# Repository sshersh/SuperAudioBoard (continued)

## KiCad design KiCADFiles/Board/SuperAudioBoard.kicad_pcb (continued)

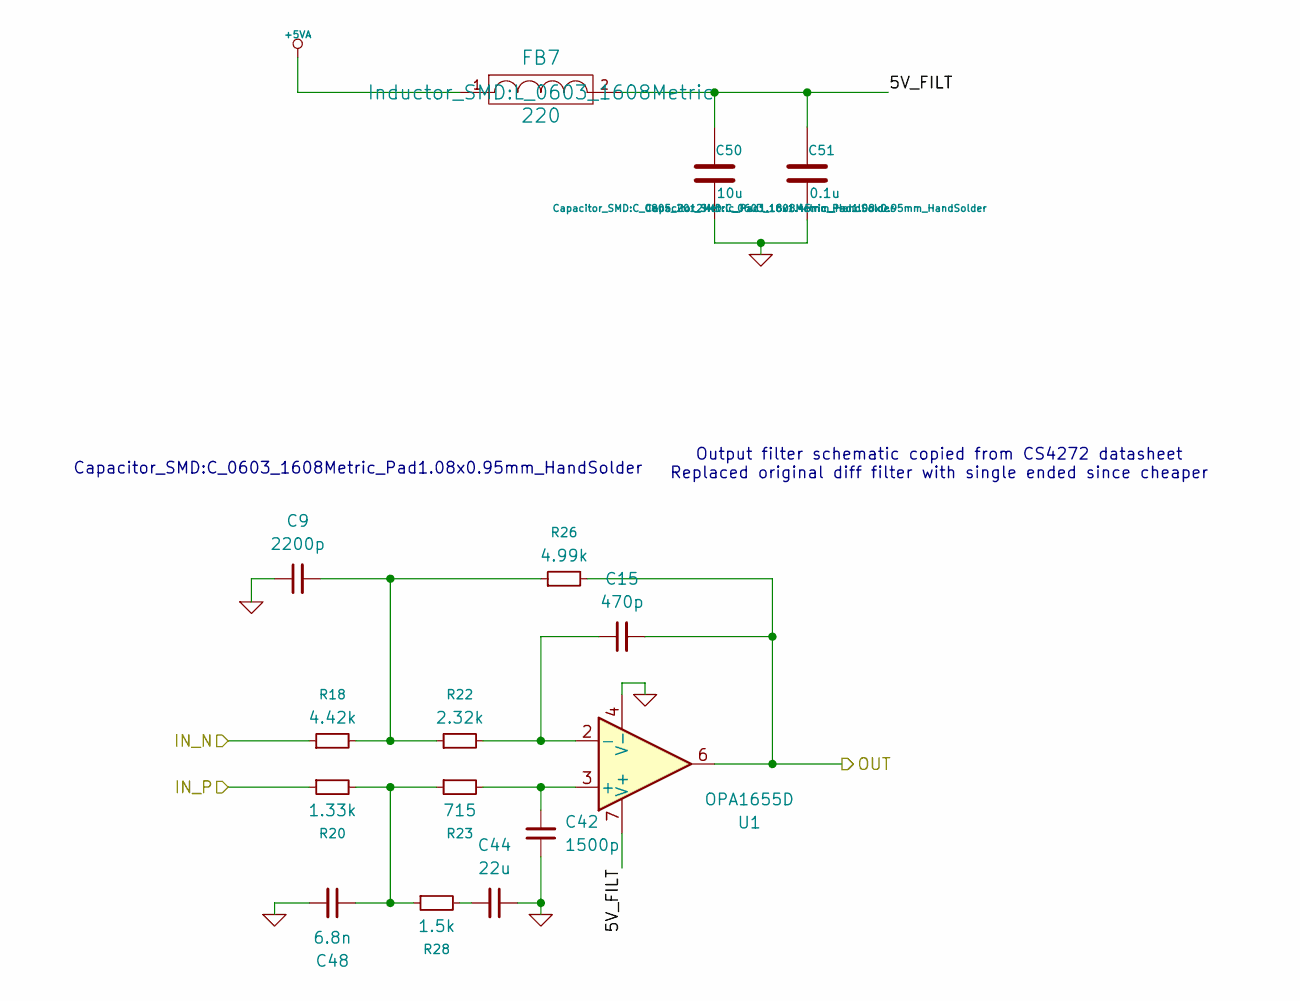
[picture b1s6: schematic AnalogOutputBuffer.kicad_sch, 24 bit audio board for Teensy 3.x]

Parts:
C9: 2200p; C_0603_1608Metric_Pad1.08x0.95mm_HandSolder; MPN GRM1885C1H222JA01D
C15: 470p; C_0603_1608Metric_Pad1.08x0.95mm_HandSolder; MPN 08053C471KAT2A
C42: 1500p; C_0603_1608Metric_Pad1.08x0.95mm_HandSolder; MPN C0603C152F1GACTU
C44: 22u; C_0805_2012Metric_Pad1.18x1.45mm_HandSolder; MPN KAM21AT70J226MU
C48: 6.8n; C_0603_1608Metric_Pad1.08x0.95mm_HandSolder; MPN GRM1885C1H682JA01D
C50: 10u; C_0805_2012Metric_Pad1.18x1.45mm_HandSolder; Voltage 25V; MFG1 PN GRM32DR71E106KA12
C51: 0.1u; C_0603_1608Metric_Pad1.08x0.95mm_HandSolder; MFG1 PN GRM188R71E104KA01
FB7: 220; L_0603_1608Metric; MFG1 PN BLM18AG221SN1
R18: 4.42k; R_0805_2012Metric; MPN ERA-6AEB4421V
R20: 1.33k; R_0805_2012Metric; MPN ERA-6AEB1331V
R22: 2.32k; R_0805_2012Metric; MPN RMCF0805FT2K32
R23: 715; R_0805_2012Metric; MPN RC0805FR-07715RL
R26: 4.99k; R_0805_2012Metric; MPN RG2012P-4991-B-T5
R28: 1.5k; R_0805_2012Metric; MPN RC0805FR-071K5L
U1: OPA1655D; SOIC-8_3.9x4.9mm_P1.27mm; MPN OPA1655D

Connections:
+5VA: FB7.1; also elsewhere on the board
/CodecAndAnalog/OutputBufferB/5V_FILT: C50.1, C51.1, FB7.2, U1.7 (V+)
/CodecAndAnalog/OutputBufferB/IN_N: R18.1; also elsewhere on the board
/CodecAndAnalog/OutputBufferB/IN_P: R20.1; also elsewhere on the board
/CodecAndAnalog/OutputBufferB/OUT: C15.2, R26.2, U1.6; also elsewhere on the board
GND: C9.1, C42.1, C44.1, C48.2, C50.2, C51.2, U1.4 (V-); also elsewhere on the board
unnamed: C9.2, R18.2, R22.1, R26.1
unnamed: C44.2, R28.2
unnamed: C48.1, R20.2, R23.1, R28.1
unnamed: C42.2, R23.2, U1.3 (+)
unnamed: C15.1, R22.2, U1.2 (-)

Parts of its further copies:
C14: 2200p; C_0603_1608Metric_Pad1.08x0.95mm_HandSolder; MPN GRM1885C1H222JA01D
C41: 470p; C_0603_1608Metric_Pad1.08x0.95mm_HandSolder; MPN 08053C471KAT2A
C45: 1500p; C_0603_1608Metric_Pad1.08x0.95mm_HandSolder; MPN C0603C152F1GACTU
C46: 22u; C_0805_2012Metric_Pad1.18x1.45mm_HandSolder; MPN KAM21AT70J226MU
C49: 6.8n; C_0603_1608Metric_Pad1.08x0.95mm_HandSolder; MPN GRM1885C1H682JA01D
C54: 10u; C_0805_2012Metric_Pad1.18x1.45mm_HandSolder; Voltage 25V; MFG1 PN GRM32DR71E106KA12
C55: 0.1u; C_0603_1608Metric_Pad1.08x0.95mm_HandSolder; MFG1 PN GRM188R71E104KA01
FB8: 220; L_0603_1608Metric; MFG1 PN BLM18AG221SN1
R19: 4.42k; R_0805_2012Metric; MPN ERA-6AEB4421V
R21: 1.33k; R_0805_2012Metric; MPN ERA-6AEB1331V
R24: 2.32k; R_0805_2012Metric; MPN RMCF0805FT2K32
R25: 715; R_0805_2012Metric; MPN RC0805FR-07715RL
R27: 4.99k; R_0805_2012Metric; MPN RG2012P-4991-B-T5
R29: 1.5k; R_0805_2012Metric; MPN RC0805FR-071K5L
U4: OPA1655D; SOIC-8_3.9x4.9mm_P1.27mm; MPN OPA1655D

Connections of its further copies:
+5VA: FB8.1; also elsewhere on the board
/CodecAndAnalog/OutputBufferA/5V_FILT: C54.1, C55.1, FB8.2, U4.7 (V+)
/CodecAndAnalog/OutputBufferA/IN_N: R19.1; also elsewhere on the board
/CodecAndAnalog/OutputBufferA/IN_P: R21.1; also elsewhere on the board
/CodecAndAnalog/OutputBufferA/OUT: C41.2, R27.2, U4.6; also elsewhere on the board
GND: C14.1, C45.1, C46.1, C49.2, C54.2, C55.2, U4.4 (V-); also elsewhere on the board
unnamed: C14.2, R19.2, R24.1, R27.1
unnamed: C46.2, R29.2
unnamed: C49.1, R21.2, R25.1, R29.1
unnamed: C45.2, R25.2, U4.3 (+)
unnamed: C41.1, R24.2, U4.2 (-)

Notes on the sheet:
Capacitor_SMD:C_0603_1608Metric_Pad1.08x0.95mm_HandSolder
Output filter schematic copied from CS4272 datasheet Replaced original diff filter with single ended since cheaper

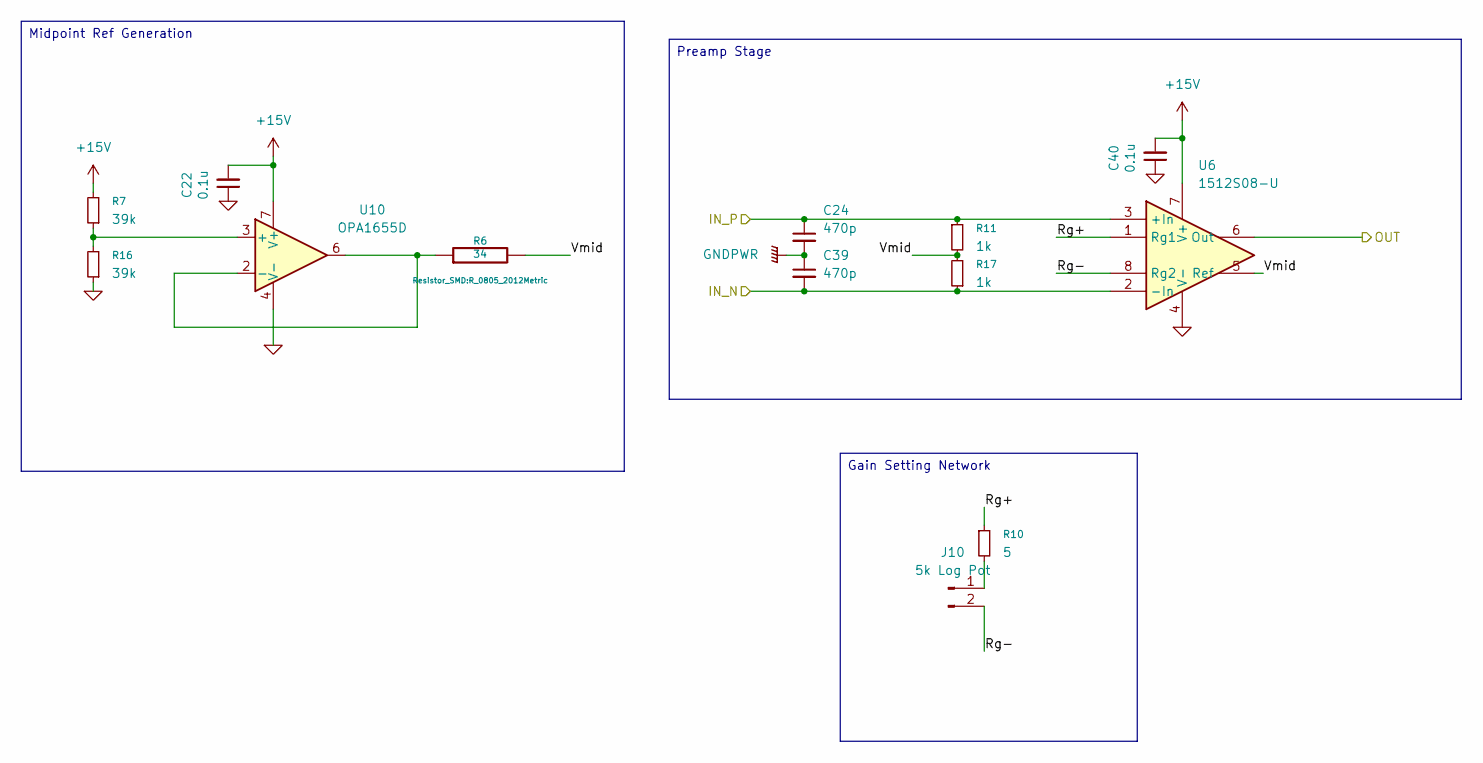
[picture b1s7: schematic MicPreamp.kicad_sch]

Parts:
C22, C40: 0.1u; C_0603_1608Metric_Pad1.08x0.95mm_HandSolder; Voltage 25V; Tolerance 20%; MPN CL10B104KB8NNNL
C24, C39: 470p; C_0603_1608Metric_Pad1.08x0.95mm_HandSolder; Voltage 50V; Tolerance 5%; MPN 08053C471KAT2A
J10: 5k Log Pot; PinHeader_1x02_P2.54mm_Vertical; MPN RV16AF-10-15K-C5K-3LA
R6: 34; R_0805_2012Metric; MFG1 PN RC0805JR-0710RL
R7, R16: 39k; R_0805_2012Metric; MPN ERA-6AEB3922V
R10: 5; R_0805_2012Metric; MPN RC0805FR-074R7L
R11, R17: 1k; R_0805_2012Metric; MPN ERA-6AEB102V
U6: 1512S08-U; SOIC-8_5.3x5.3mm_P1.27mm; MPN 1512S08-U
U10: OPA1655D; SOIC-8_3.9x4.9mm_P1.27mm; MPN OPA1655D

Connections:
+15V: C22.2, C40.2, R7.2, U6.7 (V+), U10.7 (V+); also elsewhere on the board
/CodecAndAnalog/MicPreamp/IN_N: C39.2, R17.1, U6.2 (-In); also elsewhere on the board
/CodecAndAnalog/MicPreamp/IN_P: C24.1, R11.1, U6.3 (+In); also elsewhere on the board
/CodecAndAnalog/MicPreamp/OUT: U6.6 (Out); also elsewhere on the board
/CodecAndAnalog/MicPreamp/Rg+: R10.1, U6.1 (Rg1)
/CodecAndAnalog/MicPreamp/Rg-: J10.2, U6.8 (Rg2)
/CodecAndAnalog/MicPreamp/Vmid: R6.2, R11.2, R17.2, U6.5 (Ref)
GND: C22.1, C40.1, R16.1, U6.4 (V-), U10.4 (V-); also elsewhere on the board
GNDPWR: C24.2, C39.1; also elsewhere on the board
unnamed: J10.1, R10.2
unnamed: R7.1, R16.2, U10.3 (+)
unnamed: R6.1, U10.2 (-), U10.6

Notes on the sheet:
Gain Setting Network
Preamp Stage
Midpoint Ref Generation

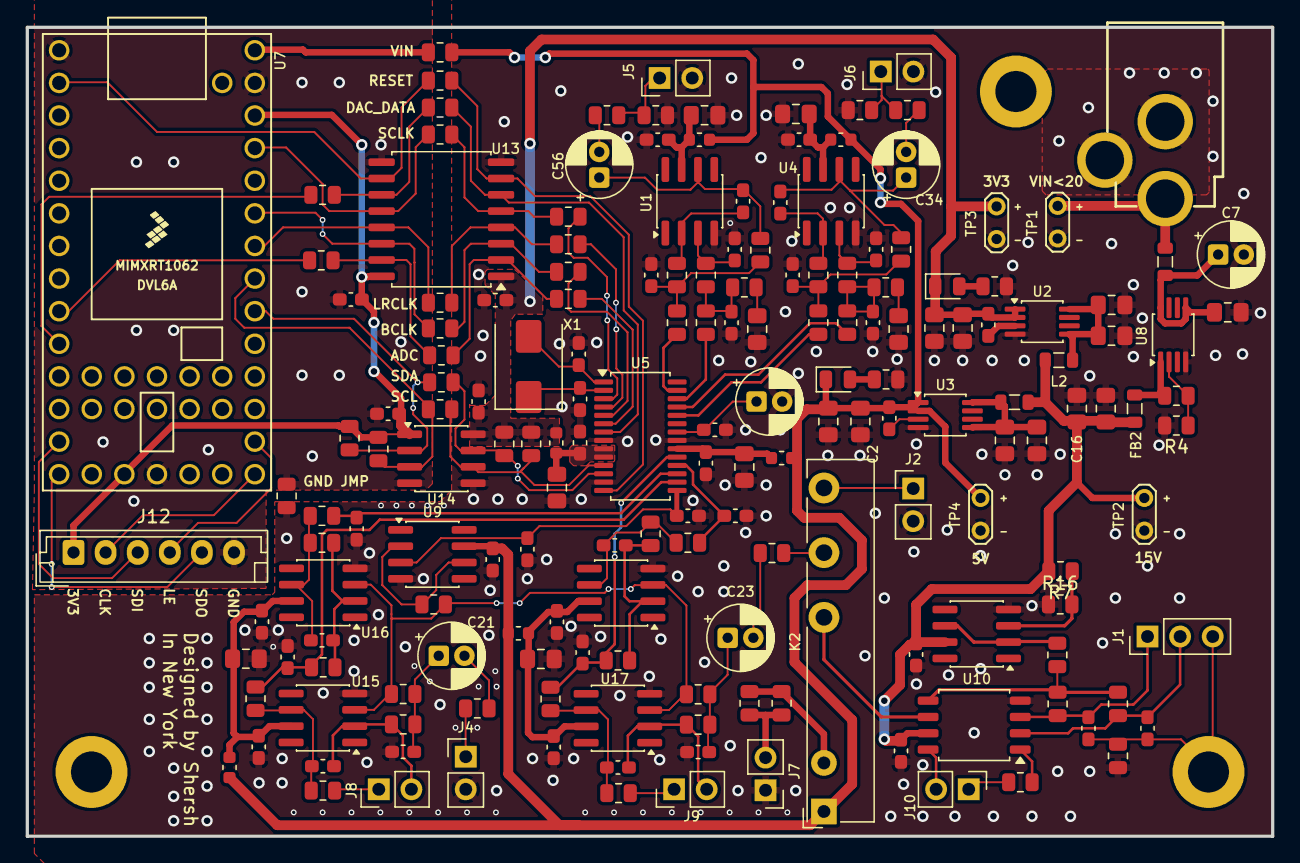
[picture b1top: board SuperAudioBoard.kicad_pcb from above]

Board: 2 copper layers, 97.0 x 63.0 mm, 181 parts (0 on the bottom side), 108 nets.

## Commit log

2026-02-02 initial schematic with RPI pico
2026-02-22 chose all components
2026-02-24 replaced sw with relay, routed line amp section
2026-02-25 removed connectors and condensed layout
2026-02-27 improved layout further
2026-02-28 made crystal footprint smaller
2026-03-02 placed all components, routed most
2026-03-08 finished layout, passed DRC
2026-03-09 improved layout for noise immunity
2026-03-12 added LED driver JST connector
